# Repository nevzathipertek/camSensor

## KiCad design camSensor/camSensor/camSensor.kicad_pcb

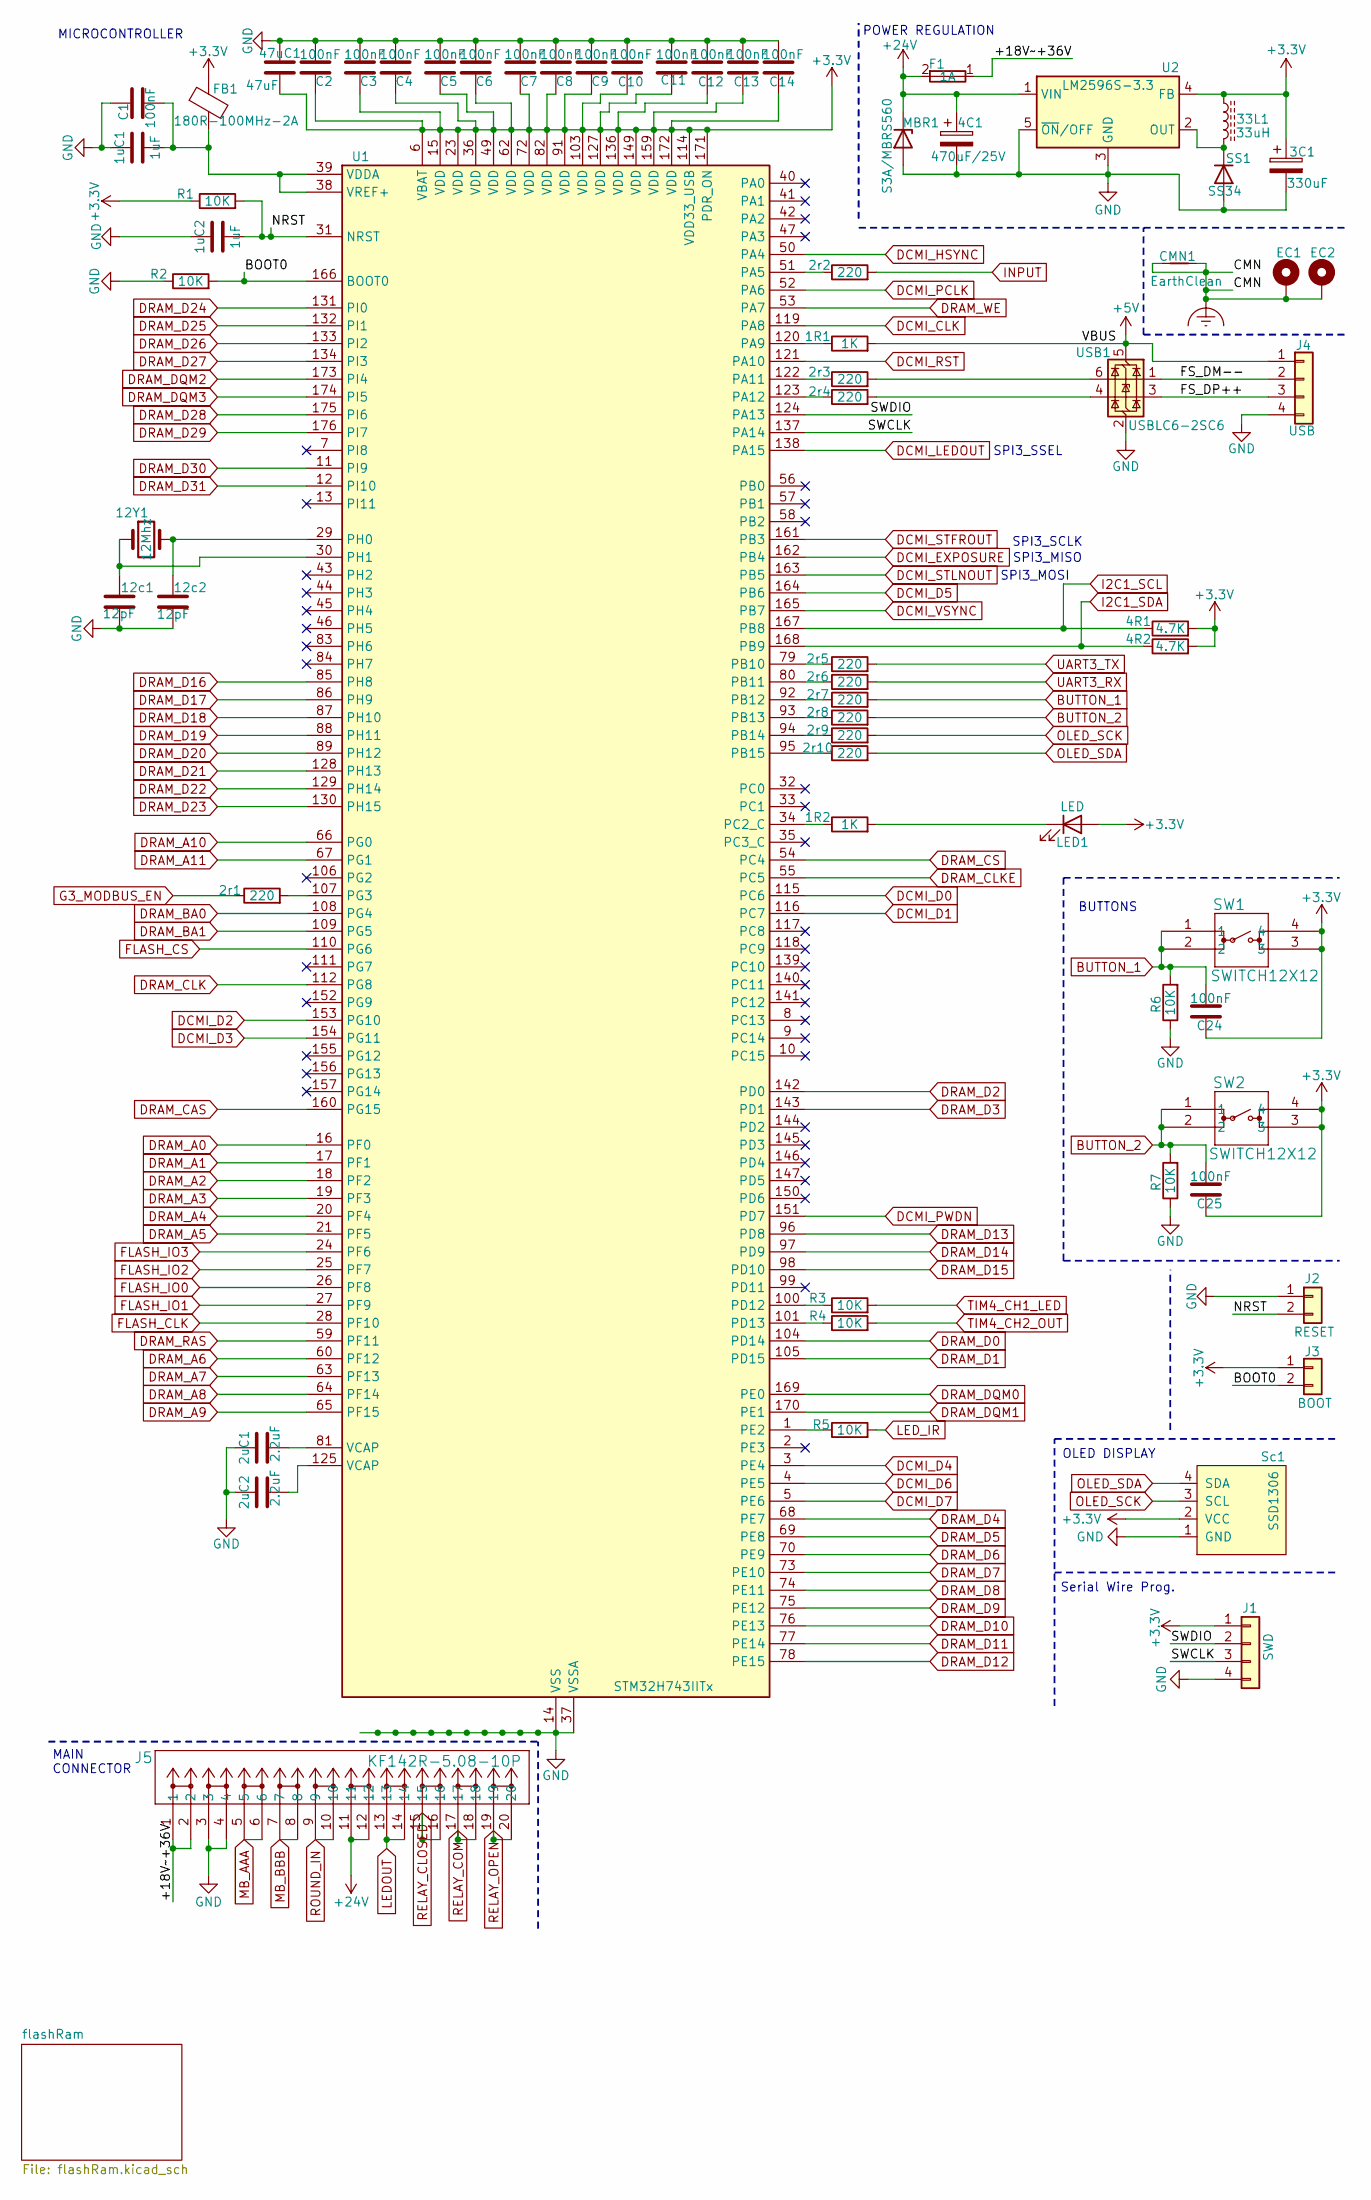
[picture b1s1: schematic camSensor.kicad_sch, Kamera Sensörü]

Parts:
1R1, 1R2: 1K; R_0603_1608Metric
1uC1, 1uC2: 1uF; C_0603_1608Metric
2r1, 2r2, 2r3, 2r4, 2r5, 2r6, 2r7, 2r8, 2r9, 2r10: 220; R_0603_1608Metric
2uC1, 2uC2: 2.2uF; C_0603_1608Metric
3C1: 330uF; CP_Elec_6.3x5.9
4C1: 470uF/25V; CP_Elec_10x10
4R1, 4R2: 4.7K; R_0603_1608Metric
12Y1: 12Mhz; Crystal_SMD_HC49-SD
12c1, 12c2: 12pF; C_0603_1608Metric
33L1: 33uH; L_Bourns_SRP7028A_7.3x6.6mm
47uC1: 47uF; C_0805_2012Metric
C1, C2, C3, C4, C5, C6, C7, C8, C9, C10, C11, C12, C13, C14, C24, C25: 100nF; C_0603_1608Metric
CMN1: EarthClean; NetTie-2_SMD_Pad0.5mm
EC1, EC2: MountingHole_Pad; MountingHole_2.2mm_M2_Pad
F1: 1A; CONN02_FUSEBLOCK_22P6X9_LTF
FB1: 180R-100MHz-2A; L_0805_2012Metric
J1: SWD; PinSocket_1x04_P2.54mm_Vertical
J2: RESET; PinHeader_1x02_P2.54mm_Vertical
J3: BOOT; PinHeader_1x02_P2.54mm_Vertical
J4: USB; PinHeader_1x04_P2.54mm_Vertical
J5: KF142R-5.08-10P; CONN_KF142R-5.08-10P_CKE
LED1: LED; LED_0603_1608Metric
MBR1: S3A/MBRS560; D_SMC
R1, R2, R3, R4, R5, R6, R7: 10K; R_0603_1608Metric
SS1: SS34; D_SMB
SW1, SW2: SWITCH12X12; 1571217-3_TEC
Sc1: SSD1306; 128x64OLED
U1: STM32H743IITx; LQFP-176_24x24mm_P0.5mm
U2: LM2596S-3.3; TO-263-5_TabPin3
USB1: USBLC6-2SC6; SOT-23-6

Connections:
+3.3V: 3C1.1, 4R1.2, 4R2.2, 33L1.1, 47uC1.2, C2.1, C3.1, C4.1, C5.1, C6.1, C7.1, C8.1, C9.1, C10.1, C11.1, C12.1, C13.1, C14.1, C24.1, C25.1, FB1.1, J1.1, J3.1, LED1.2 (A), R1.1, SW1.3, SW1.4, SW2.3, SW2.4, Sc1.2 (VCC), U1.6 (VBAT), U1.15 (VDD), U1.23 (VDD), U1.36 (VDD), U1.49 (VDD), U1.62 (VDD), U1.72 (VDD), U1.82 (VDD), U1.91 (VDD), U1.103 (VDD), U1.114 (VDD33_USB), U1.127 (VDD), U1.136 (VDD), U1.149 (VDD), U1.159 (VDD), U1.171 (PDR_ON), U1.172 (VDD), U2.4 (FB); also elsewhere on the board
+5V: 1R1.2, J4.1, USB1.5 (VBUS)
+24V: 4C1.1, F1.2, J5.11, J5.12, MBR1.1 (K), U2.1 (VIN); also elsewhere on the board
/+18V~+36V: F1.1, J5.1, J5.2
/BOOT0: J3.2, R2.2, U1.166 (BOOT0)
/FS_DM--: J4.2, USB1.1 (I/O1)
/FS_DP++: J4.3, USB1.3 (I/O2)
/NRST: 1uC2.2, J2.2, R1.2, U1.31 (NRST)
/SWCLK: J1.3, U1.137 (PA14)
/SWDIO: J1.2, U1.124 (PA13)
BUTTON_1: 2r7.2, C24.2, R6.2, SW1.1, SW1.2
BUTTON_2: 2r8.2, C25.2, R7.2, SW2.1, SW2.2
DCMI_CLK: U1.119 (PA8); also elsewhere on the board
DCMI_D0: U1.115 (PC6); also elsewhere on the board
DCMI_D1: U1.116 (PC7); also elsewhere on the board
DCMI_D2: U1.153 (PG10); also elsewhere on the board
DCMI_D3: U1.154 (PG11); also elsewhere on the board
DCMI_D4: U1.3 (PE4); also elsewhere on the board
DCMI_D5: U1.164 (PB6); also elsewhere on the board
DCMI_D6: U1.4 (PE5); also elsewhere on the board
DCMI_D7: U1.5 (PE6); also elsewhere on the board
DCMI_EXPOSURE: U1.162 (PB4); also elsewhere on the board
DCMI_HSYNC: U1.50 (PA4); also elsewhere on the board
DCMI_LEDOUT: U1.138 (PA15); also elsewhere on the board
DCMI_PCLK: U1.52 (PA6); also elsewhere on the board
DCMI_PWDN: U1.151 (PD7); also elsewhere on the board
DCMI_RST: U1.121 (PA10); also elsewhere on the board
DCMI_STFROUT: U1.161 (PB3); also elsewhere on the board
DCMI_STLNOUT: U1.163 (PB5); also elsewhere on the board
DCMI_VSYNC: U1.165 (PB7); also elsewhere on the board
DRAM_A0: U1.16 (PF0); also elsewhere on the board
DRAM_A1: U1.17 (PF1); also elsewhere on the board
DRAM_A2: U1.18 (PF2); also elsewhere on the board
DRAM_A3: U1.19 (PF3); also elsewhere on the board
DRAM_A4: U1.20 (PF4); also elsewhere on the board
DRAM_A5: U1.21 (PF5); also elsewhere on the board
DRAM_A6: U1.60 (PF12); also elsewhere on the board
DRAM_A7: U1.63 (PF13); also elsewhere on the board
DRAM_A8: U1.64 (PF14); also elsewhere on the board
DRAM_A9: U1.65 (PF15); also elsewhere on the board
DRAM_A10: U1.66 (PG0); also elsewhere on the board
DRAM_A11: U1.67 (PG1); also elsewhere on the board
DRAM_BA0: U1.108 (PG4); also elsewhere on the board
DRAM_BA1: U1.109 (PG5); also elsewhere on the board
DRAM_CAS: U1.160 (PG15); also elsewhere on the board
DRAM_CLK: U1.112 (PG8); also elsewhere on the board
DRAM_CLKE: U1.55 (PC5); also elsewhere on the board
DRAM_CS: U1.54 (PC4); also elsewhere on the board
DRAM_D0: U1.104 (PD14); also elsewhere on the board
DRAM_D1: U1.105 (PD15); also elsewhere on the board
DRAM_D2: U1.142 (PD0); also elsewhere on the board
DRAM_D3: U1.143 (PD1); also elsewhere on the board
DRAM_D4: U1.68 (PE7); also elsewhere on the board
DRAM_D5: U1.69 (PE8); also elsewhere on the board
DRAM_D6: U1.70 (PE9); also elsewhere on the board
DRAM_D7: U1.73 (PE10); also elsewhere on the board
DRAM_D8: U1.74 (PE11); also elsewhere on the board
DRAM_D9: U1.75 (PE12); also elsewhere on the board
DRAM_D10: U1.76 (PE13); also elsewhere on the board
DRAM_D11: U1.77 (PE14); also elsewhere on the board
DRAM_D12: U1.78 (PE15); also elsewhere on the board
DRAM_D13: U1.96 (PD8); also elsewhere on the board
DRAM_D14: U1.97 (PD9); also elsewhere on the board
DRAM_D15: U1.98 (PD10); also elsewhere on the board
DRAM_D16: U1.85 (PH8); also elsewhere on the board
DRAM_D17: U1.86 (PH9); also elsewhere on the board
DRAM_D18: U1.87 (PH10); also elsewhere on the board
DRAM_D19: U1.88 (PH11); also elsewhere on the board
DRAM_D20: U1.89 (PH12); also elsewhere on the board
DRAM_D21: U1.128 (PH13); also elsewhere on the board
DRAM_D22: U1.129 (PH14); also elsewhere on the board
DRAM_D23: U1.130 (PH15); also elsewhere on the board
DRAM_D24: U1.131 (PI0); also elsewhere on the board
DRAM_D25: U1.132 (PI1); also elsewhere on the board
DRAM_D26: U1.133 (PI2); also elsewhere on the board
DRAM_D27: U1.134 (PI3); also elsewhere on the board
DRAM_D28: U1.175 (PI6); also elsewhere on the board
DRAM_D29: U1.176 (PI7); also elsewhere on the board
DRAM_D30: U1.11 (PI9); also elsewhere on the board
DRAM_D31: U1.12 (PI10); also elsewhere on the board
DRAM_DQM0: U1.169 (PE0); also elsewhere on the board
DRAM_DQM1: U1.170 (PE1); also elsewhere on the board
DRAM_DQM2: U1.173 (PI4); also elsewhere on the board
DRAM_DQM3: U1.174 (PI5); also elsewhere on the board
DRAM_RAS: U1.59 (PF11); also elsewhere on the board
DRAM_WE: U1.53 (PA7); also elsewhere on the board
Earth_Clean: CMN1.1, CMN1.2, EC1.1, EC2.1
FLASH_CLK: U1.28 (PF10); also elsewhere on the board
FLASH_CS: U1.110 (PG6); also elsewhere on the board
FLASH_IO0: U1.26 (PF8); also elsewhere on the board
FLASH_IO1: U1.27 (PF9); also elsewhere on the board
FLASH_IO2: U1.25 (PF7); also elsewhere on the board
FLASH_IO3: U1.24 (PF6); also elsewhere on the board
G3_MODBUS_EN: 2r1.1; also elsewhere on the board
GND: 1uC1.1, 1uC2.1, 2uC1.1, 2uC2.1, 3C1.2, 4C1.2, 12c1.2, 12c2.2, 47uC1.1, C1.1, C2.2, C3.2, C4.2, C5.2, C6.2, C7.2, C8.2, C9.2, C10.2, C11.2, C12.2, C13.2, C14.2, J1.4, J2.1, J4.4, J5.3, J5.4, MBR1.2 (A), R2.1, R6.1, R7.1, SS1.2 (A), Sc1.1 (GND), U1.14 (VSS), U1.22 (VSS), U1.37 (VSSA), U1.48 (VSS), U1.61 (VSS), U1.71 (VSS), U1.90 (VSS), U1.102 (VSS), U1.113 (VSS), U1.126 (VSS), U1.135 (VSS), U1.148 (VSS), U1.158 (VSS), U2.3 (GND), U2.5 (~ON/OFF), USB1.2 (GND); also elsewhere on the board
I2C1_SCL: 4R1.1, U1.167 (PB8); also elsewhere on the board
I2C1_SDA: 4R2.1, U1.168 (PB9); also elsewhere on the board
INPUT: 2r2.2; also elsewhere on the board
LEDOUT: J5.13, J5.14; also elsewhere on the board
LED_IR: R5.2; also elsewhere on the board
MB_AAA: J5.5, J5.6; also elsewhere on the board
MB_BBB: J5.7, J5.8; also elsewhere on the board
unnamed: 2r3.2, USB1.6 (I/O1)
unnamed: 2r4.2, USB1.4 (I/O2)
unnamed: 2uC1.2, U1.81 (VCAP)
unnamed: 2uC2.2, U1.125 (VCAP)
unnamed: 1R2.2, LED1.1 (K)
unnamed: 33L1.2, SS1.1 (K), U2.2 (OUT)
unnamed: 2r2.1, U1.51 (PA5)
unnamed: 1R1.1, U1.120 (PA9)
unnamed: 2r3.1, U1.122 (PA11)
unnamed: 2r4.1, U1.123 (PA12)
unnamed: 2r5.1, U1.79 (PB10)
unnamed: 2r6.1, U1.80 (PB11)
unnamed: 2r7.1, U1.92 (PB12)
unnamed: 2r8.1, U1.93 (PB13)
unnamed: 2r9.1, U1.94 (PB14)
unnamed: 2r10.1, U1.95 (PB15)
unnamed: 1R2.1, U1.34 (PC2_C)
unnamed: R3.1, U1.100 (PD12)
unnamed: R4.1, U1.101 (PD13)
unnamed: R5.1, U1.1 (PE2)
unnamed: 2r1.2, U1.107 (PG3)
unnamed: 12Y1.2, 12c2.1, U1.29 (PH0)
unnamed: 12Y1.1, 12c1.1, U1.30 (PH1)
unnamed: 1uC1.2, C1.2, FB1.2, U1.38 (VREF+), U1.39 (VDDA)
OLED_SCK: 2r9.2, Sc1.3 (SCL)
OLED_SDA: 2r10.2, Sc1.4 (SDA)
RELAY_CLOSED: J5.15, J5.16; also elsewhere on the board
RELAY_COM: J5.17, J5.18; also elsewhere on the board
RELAY_OPEN: J5.19, J5.20; also elsewhere on the board
ROUND_IN: J5.9, J5.10; also elsewhere on the board
TIM4_CH1_LED: R3.2; also elsewhere on the board
TIM4_CH2_OUT: R4.2; also elsewhere on the board
UART3_RX: 2r6.2; also elsewhere on the board
UART3_TX: 2r5.2; also elsewhere on the board

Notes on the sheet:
OLED DISPLAY
Serial Wire Prog.
SPI3_SCLK
SPI3_MISO
POWER REGULATION
MAIN CONNECTOR
SPI3_MOSI
BUTTONS
MICROCONTROLLER
SPI3_SSEL

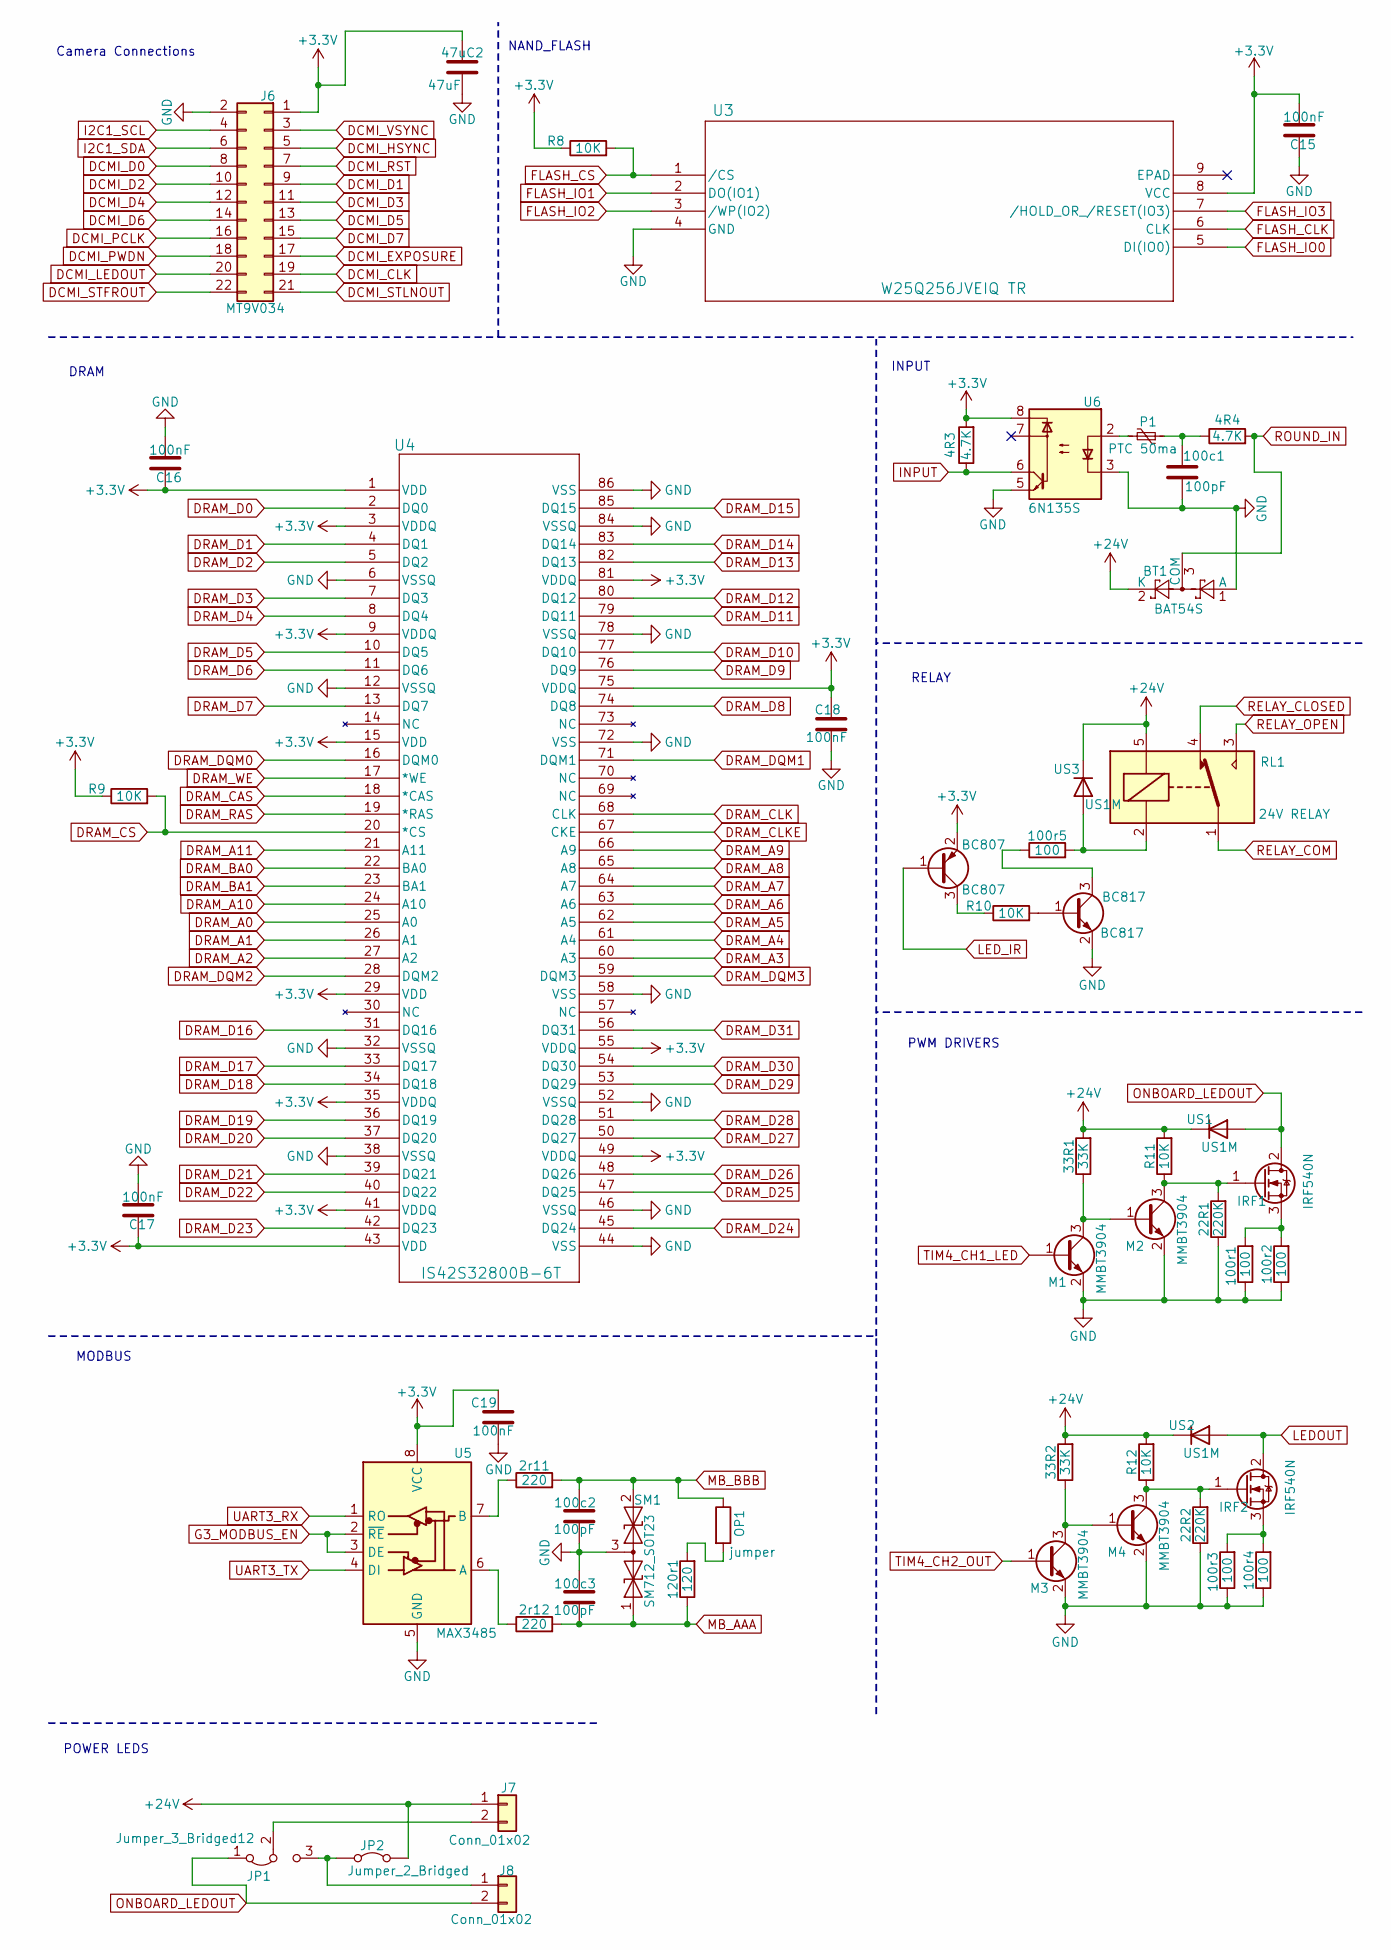
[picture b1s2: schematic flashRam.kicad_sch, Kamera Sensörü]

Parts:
2r11, 2r12: 220; R_0603_1608Metric
4R3, 4R4: 4.7K; R_0603_1608Metric
22R1, 22R2: 220K; R_0603_1608Metric
33R1, 33R2: 33K; R_0603_1608Metric
47uC2: 47uF; C_0805_2012Metric
100c1, 100c2, 100c3: 100pF; C_0603_1608Metric
100r1, 100r2, 100r3, 100r4, 100r5: 100; R_2512_6332Metric_Pad1.40x3.35mm_HandSolder
120r1: 120; R_0603_1608Metric
BC807: BC807; SOT-23
BC817: BC817; SOT-23
BT1: BAT54S; SOT-23
C15, C16, C17, C18, C19: 100nF; C_0603_1608Metric
IRF1, IRF2: IRF540N; TO-263-2
J6: MT9V034; PinHeader_2x11_P2.54mm_Vertical
J7, J8: Conn_01x02; PinHeader_1x02_P2.54mm_Vertical
JP1: Jumper_3_Bridged12; SolderJumper-3_P1.3mm_Bridged12_RoundedPad1.0x1.5mm
JP2: Jumper_2_Bridged; SolderJumper-2_P1.3mm_Bridged_RoundedPad1.0x1.5mm
M1, M2, M3, M4: MMBT3904; SOT-23
OP1: jumper; SolderJumper-2_P1.3mm_Bridged_RoundedPad1.0x1.5mm
P1: PTC 50ma; Fuse_0805_2012Metric
R8, R9, R10, R11, R12: 10K; R_0603_1608Metric
RL1: 24V RELAY; Relay_SPDT_SANYOU_SRD_Series_Form_C
SM1: SM712_SOT23; SOT-23
U3: W25Q256JVEIQ TR; WSON8_E_WIN
U4: IS42S32800B-6T; TSOP-86_11P9X22P4_ISI
U5: MAX3485; SOIC-8_3.9x4.9mm_P1.27mm
U6: 6N135S; SMDIP-8_W9.53mm
US1, US2, US3: US1M; D_SMA

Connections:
+3.3V: 4R3.2, 47uC2.1, BC807.2 (E), C15.2, C16.1, C17.1, C18.1, C19.1, J6.1, R8.1, R9.1, U3.8 (VCC), U4.1 (VDD), U4.3 (VDDQ), U4.9 (VDDQ), U4.15 (VDD), U4.29 (VDD), U4.35 (VDDQ), U4.41 (VDDQ), U4.43 (VDD), U4.49 (VDDQ), U4.55 (VDDQ), U4.75 (VDDQ), U4.81 (VDDQ), U5.8 (VCC), U6.8; also elsewhere on the board
+24V: 33R1.2, 33R2.2, BT1.2 (K), J7.1, JP2.2 (B), R11.2, R12.2, RL1.5, US1.1 (K), US2.1 (K), US3.1 (K); also elsewhere on the board
DCMI_CLK: J6.19; also elsewhere on the board
DCMI_D0: J6.8; also elsewhere on the board
DCMI_D1: J6.9; also elsewhere on the board
DCMI_D2: J6.10; also elsewhere on the board
DCMI_D3: J6.11; also elsewhere on the board
DCMI_D4: J6.12; also elsewhere on the board
DCMI_D5: J6.13; also elsewhere on the board
DCMI_D6: J6.14; also elsewhere on the board
DCMI_D7: J6.15; also elsewhere on the board
DCMI_EXPOSURE: J6.17; also elsewhere on the board
DCMI_HSYNC: J6.5; also elsewhere on the board
DCMI_LEDOUT: J6.20; also elsewhere on the board
DCMI_PCLK: J6.16; also elsewhere on the board
DCMI_PWDN: J6.18; also elsewhere on the board
DCMI_RST: J6.7; also elsewhere on the board
DCMI_STFROUT: J6.22; also elsewhere on the board
DCMI_STLNOUT: J6.21; also elsewhere on the board
DCMI_VSYNC: J6.3; also elsewhere on the board
DRAM_A0: U4.25 (A0); also elsewhere on the board
DRAM_A1: U4.26 (A1); also elsewhere on the board
DRAM_A2: U4.27 (A2); also elsewhere on the board
DRAM_A3: U4.60 (A3); also elsewhere on the board
DRAM_A4: U4.61 (A4); also elsewhere on the board
DRAM_A5: U4.62 (A5); also elsewhere on the board
DRAM_A6: U4.63 (A6); also elsewhere on the board
DRAM_A7: U4.64 (A7); also elsewhere on the board
DRAM_A8: U4.65 (A8); also elsewhere on the board
DRAM_A9: U4.66 (A9); also elsewhere on the board
DRAM_A10: U4.24 (A10); also elsewhere on the board
DRAM_A11: U4.21 (A11); also elsewhere on the board
DRAM_BA0: U4.22 (BA0); also elsewhere on the board
DRAM_BA1: U4.23 (BA1); also elsewhere on the board
DRAM_CAS: U4.18 (*CAS); also elsewhere on the board
DRAM_CLK: U4.68 (CLK); also elsewhere on the board
DRAM_CLKE: U4.67 (CKE); also elsewhere on the board
DRAM_CS: R9.2, U4.20 (*CS); also elsewhere on the board
DRAM_D0: U4.2 (DQ0); also elsewhere on the board
DRAM_D1: U4.4 (DQ1); also elsewhere on the board
DRAM_D2: U4.5 (DQ2); also elsewhere on the board
DRAM_D3: U4.7 (DQ3); also elsewhere on the board
DRAM_D4: U4.8 (DQ4); also elsewhere on the board
DRAM_D5: U4.10 (DQ5); also elsewhere on the board
DRAM_D6: U4.11 (DQ6); also elsewhere on the board
DRAM_D7: U4.13 (DQ7); also elsewhere on the board
DRAM_D8: U4.74 (DQ8); also elsewhere on the board
DRAM_D9: U4.76 (DQ9); also elsewhere on the board
DRAM_D10: U4.77 (DQ10); also elsewhere on the board
DRAM_D11: U4.79 (DQ11); also elsewhere on the board
DRAM_D12: U4.80 (DQ12); also elsewhere on the board
DRAM_D13: U4.82 (DQ13); also elsewhere on the board
DRAM_D14: U4.83 (DQ14); also elsewhere on the board
DRAM_D15: U4.85 (DQ15); also elsewhere on the board
DRAM_D16: U4.31 (DQ16); also elsewhere on the board
DRAM_D17: U4.33 (DQ17); also elsewhere on the board
DRAM_D18: U4.34 (DQ18); also elsewhere on the board
DRAM_D19: U4.36 (DQ19); also elsewhere on the board
DRAM_D20: U4.37 (DQ20); also elsewhere on the board
DRAM_D21: U4.39 (DQ21); also elsewhere on the board
DRAM_D22: U4.40 (DQ22); also elsewhere on the board
DRAM_D23: U4.42 (DQ23); also elsewhere on the board
DRAM_D24: U4.45 (DQ24); also elsewhere on the board
DRAM_D25: U4.47 (DQ25); also elsewhere on the board
DRAM_D26: U4.48 (DQ26); also elsewhere on the board
DRAM_D27: U4.50 (DQ27); also elsewhere on the board
DRAM_D28: U4.51 (DQ28); also elsewhere on the board
DRAM_D29: U4.53 (DQ29); also elsewhere on the board
DRAM_D30: U4.54 (DQ30); also elsewhere on the board
DRAM_D31: U4.56 (DQ31); also elsewhere on the board
DRAM_DQM0: U4.16 (DQM0); also elsewhere on the board
DRAM_DQM1: U4.71 (DQM1); also elsewhere on the board
DRAM_DQM2: U4.28 (DQM2); also elsewhere on the board
DRAM_DQM3: U4.59 (DQM3); also elsewhere on the board
DRAM_RAS: U4.19 (*RAS); also elsewhere on the board
DRAM_WE: U4.17 (*WE); also elsewhere on the board
FLASH_CLK: U3.6 (CLK); also elsewhere on the board
FLASH_CS: R8.2, U3.1 (/CS); also elsewhere on the board
FLASH_IO0: U3.5 (DI(IO0)); also elsewhere on the board
FLASH_IO1: U3.2 (DO(IO1)); also elsewhere on the board
FLASH_IO2: U3.3 (/WP(IO2)); also elsewhere on the board
FLASH_IO3: U3.7 (/HOLD_OR_/RESET(IO3)); also elsewhere on the board
G3_MODBUS_EN: U5.2 (~RE), U5.3 (DE); also elsewhere on the board
GND: 22R1.1, 22R2.1, 47uC2.2, 100c1.2, 100c2.2, 100c3.1, 100r1.1, 100r2.1, 100r3.1, 100r4.1, BC817.2 (E), BT1.1 (A), C15.1, C16.2, C17.2, C18.2, C19.2, J6.2, M1.2 (E), M2.2 (E), M3.2 (E), M4.2 (E), SM1.3 (common), U3.4 (GND), U4.6 (VSSQ), U4.12 (VSSQ), U4.32 (VSSQ), U4.38 (VSSQ), U4.44 (VSS), U4.46 (VSSQ), U4.52 (VSSQ), U4.58 (VSS), U4.72 (VSS), U4.78 (VSSQ), U4.84 (VSSQ), U4.86 (VSS), U5.5 (GND), U6.3, U6.5; also elsewhere on the board
I2C1_SCL: J6.4; also elsewhere on the board
I2C1_SDA: J6.6; also elsewhere on the board
INPUT: 4R3.1, U6.6; also elsewhere on the board
LEDOUT: IRF2.2 (D), US2.2 (A); also elsewhere on the board
LED_IR: BC807.1 (B); also elsewhere on the board
MB_AAA: 2r12.2, 100c3.2, 120r1.1, SM1.1 (A1); also elsewhere on the board
MB_BBB: 2r11.2, 100c2.1, OP1.1, SM1.2 (A2); also elsewhere on the board
unnamed: 4R4.1, 100c1.1, P1.1
unnamed: 120r1.2, OP1.2
unnamed: BC807.3 (C), R10.1
unnamed: BC817.1 (B), R10.2
unnamed: 100r5.1, BC817.3 (C)
unnamed: 22R1.2, IRF1.1 (G), M2.3 (C), R11.1
unnamed: 100r1.2, 100r2.2, IRF1.3 (S)
unnamed: 22R2.2, IRF2.1 (G), M4.3 (C), R12.1
unnamed: 100r3.2, 100r4.2, IRF2.3 (S)
unnamed: J7.2, JP1.2 (C)
unnamed: J8.1, JP1.3 (B), JP2.1 (A)
unnamed: 33R1.1, M1.3 (C), M2.1 (B)
unnamed 119: 33R2.1, M3.3 (C), M4.1 (B); also elsewhere on the board
unnamed: P1.2, U6.2
unnamed: 2r12.1, U5.6 (A)
unnamed: 2r11.1, U5.7 (B)
unnamed: 100r5.2, RL1.2, US3.2 (A)
ONBOARD_LEDOUT: IRF1.2 (D), J8.2, JP1.1 (A), US1.2 (A)
RELAY_CLOSED: RL1.4; also elsewhere on the board
RELAY_COM: RL1.1; also elsewhere on the board
RELAY_OPEN: RL1.3; also elsewhere on the board
ROUND_IN: 4R4.2, BT1.3 (COM); also elsewhere on the board
TIM4_CH1_LED: M1.1 (B); also elsewhere on the board
TIM4_CH2_OUT: M3.1 (B); also elsewhere on the board
UART3_RX: U5.1 (RO); also elsewhere on the board
UART3_TX: U5.4 (DI); also elsewhere on the board

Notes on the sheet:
Camera Connections
NAND_FLASH
RELAY
PWM DRIVERS
MODBUS
INPUT
POWER LEDS
DRAM

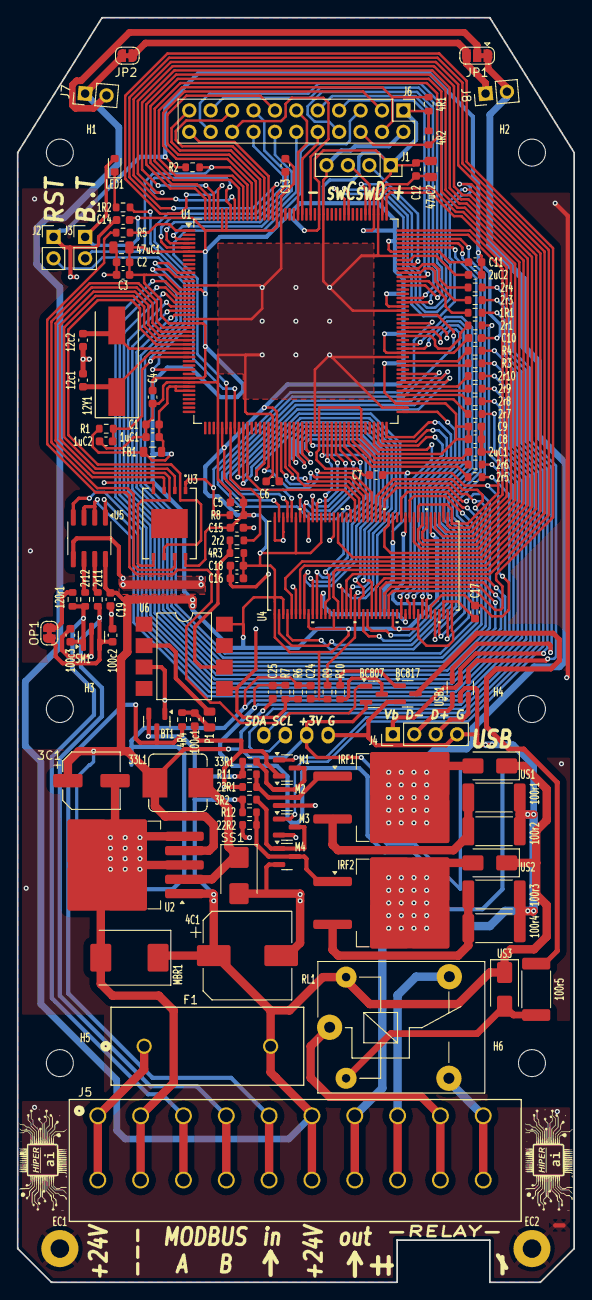
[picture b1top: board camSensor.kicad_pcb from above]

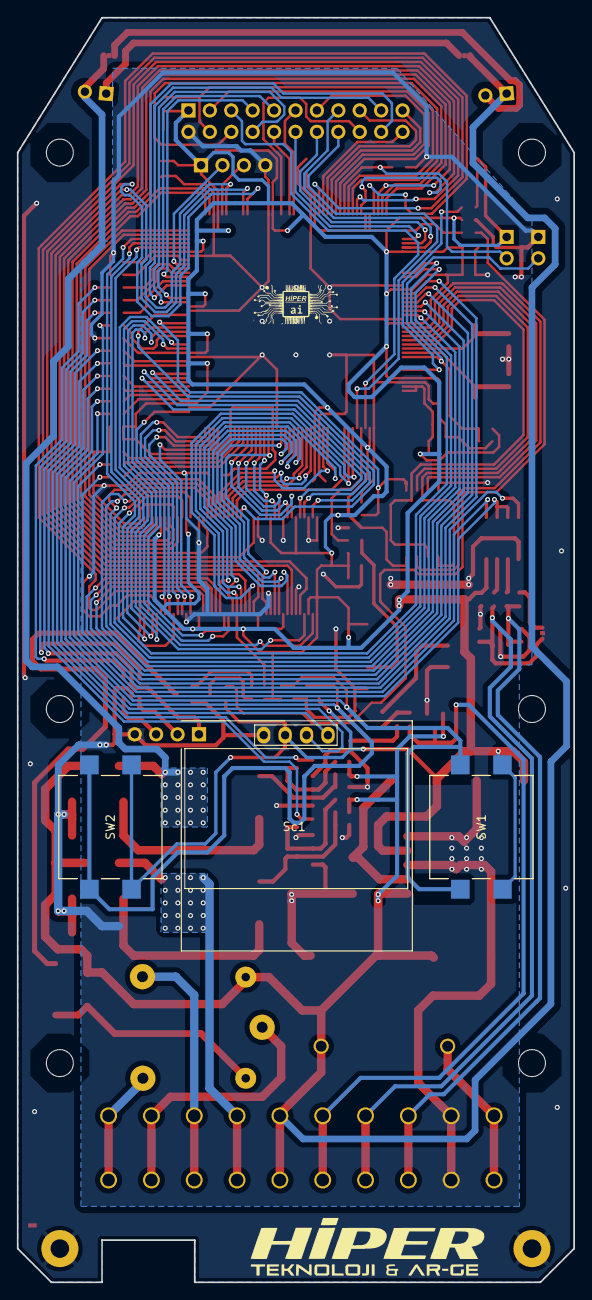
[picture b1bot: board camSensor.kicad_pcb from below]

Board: 2 copper layers, 66.0 x 150.0 mm, 130 parts (5 on the bottom side), 154 nets.

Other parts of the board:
3R2: 33K; R_0603_1608Metric
H1, H2, H3, H4, H5, H6: MountingHole_3.2mm_M3
ai: LOGO
ai#2, ai#3: LOGO
hiper: LOGO

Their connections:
+24V: 3R2.2; also elsewhere on the board
unnamed 119: 3R2.1; also elsewhere on the board

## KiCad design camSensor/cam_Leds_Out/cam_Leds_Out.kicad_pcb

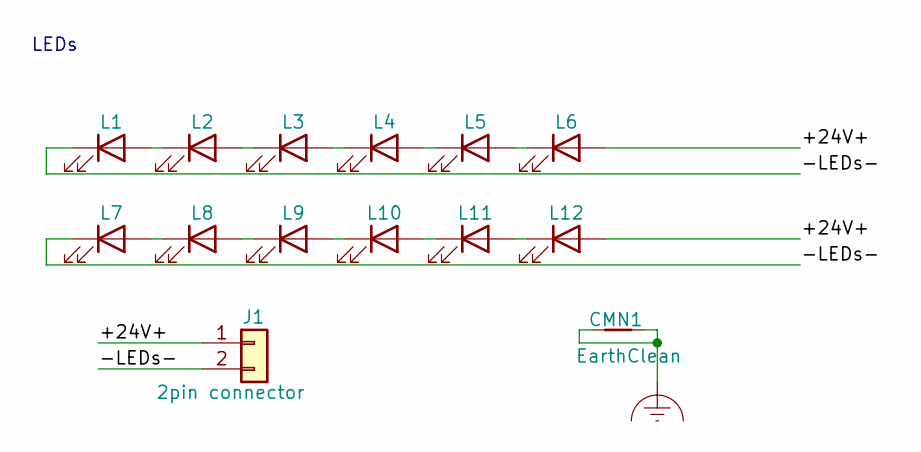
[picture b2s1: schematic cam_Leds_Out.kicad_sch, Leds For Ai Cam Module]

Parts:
CMN1: EarthClean; NetTie-2_SMD_Pad0.5mm
J1: 2pin connector; PinHeader_1x02_P2.54mm_Vertical
L1, L2, L3, L4, L5, L6, L7, L8, L9, L10, L11, L12: LED; LED_PLCC_2835

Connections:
/+24V+: J1.1, L6.2 (A), L12.2 (A)
/-LEDs-: J1.2, L1.1 (K), L7.1 (K)
Earth_Clean: CMN1.1, CMN1.2
unnamed: L1.2 (A), L2.1 (K)
unnamed: L2.2 (A), L3.1 (K)
unnamed: L3.2 (A), L4.1 (K)
unnamed: L4.2 (A), L5.1 (K)
unnamed: L5.2 (A), L6.1 (K)
unnamed: L7.2 (A), L8.1 (K)
unnamed: L8.2 (A), L9.1 (K)
unnamed: L10.2 (A), L11.1 (K)
unnamed: L9.2 (A), L10.1 (K)
unnamed: L11.2 (A), L12.1 (K)

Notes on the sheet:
LEDs

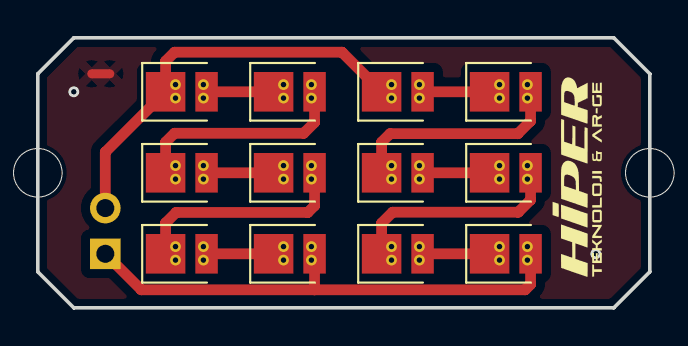
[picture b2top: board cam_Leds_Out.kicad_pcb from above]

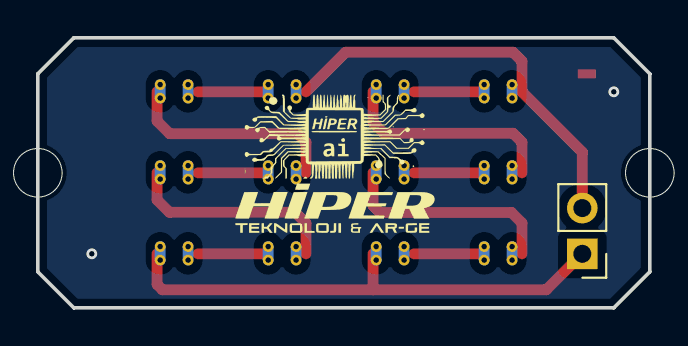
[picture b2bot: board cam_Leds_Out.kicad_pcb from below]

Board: 2 copper layers, 34.0 x 15.0 mm, 19 parts (3 on the bottom side), 13 nets.

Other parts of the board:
H1, H1#2: MountingHole_2.7mm_M2.5
ai: LOGO
hiper: LOGO
hiper#2: LOGO

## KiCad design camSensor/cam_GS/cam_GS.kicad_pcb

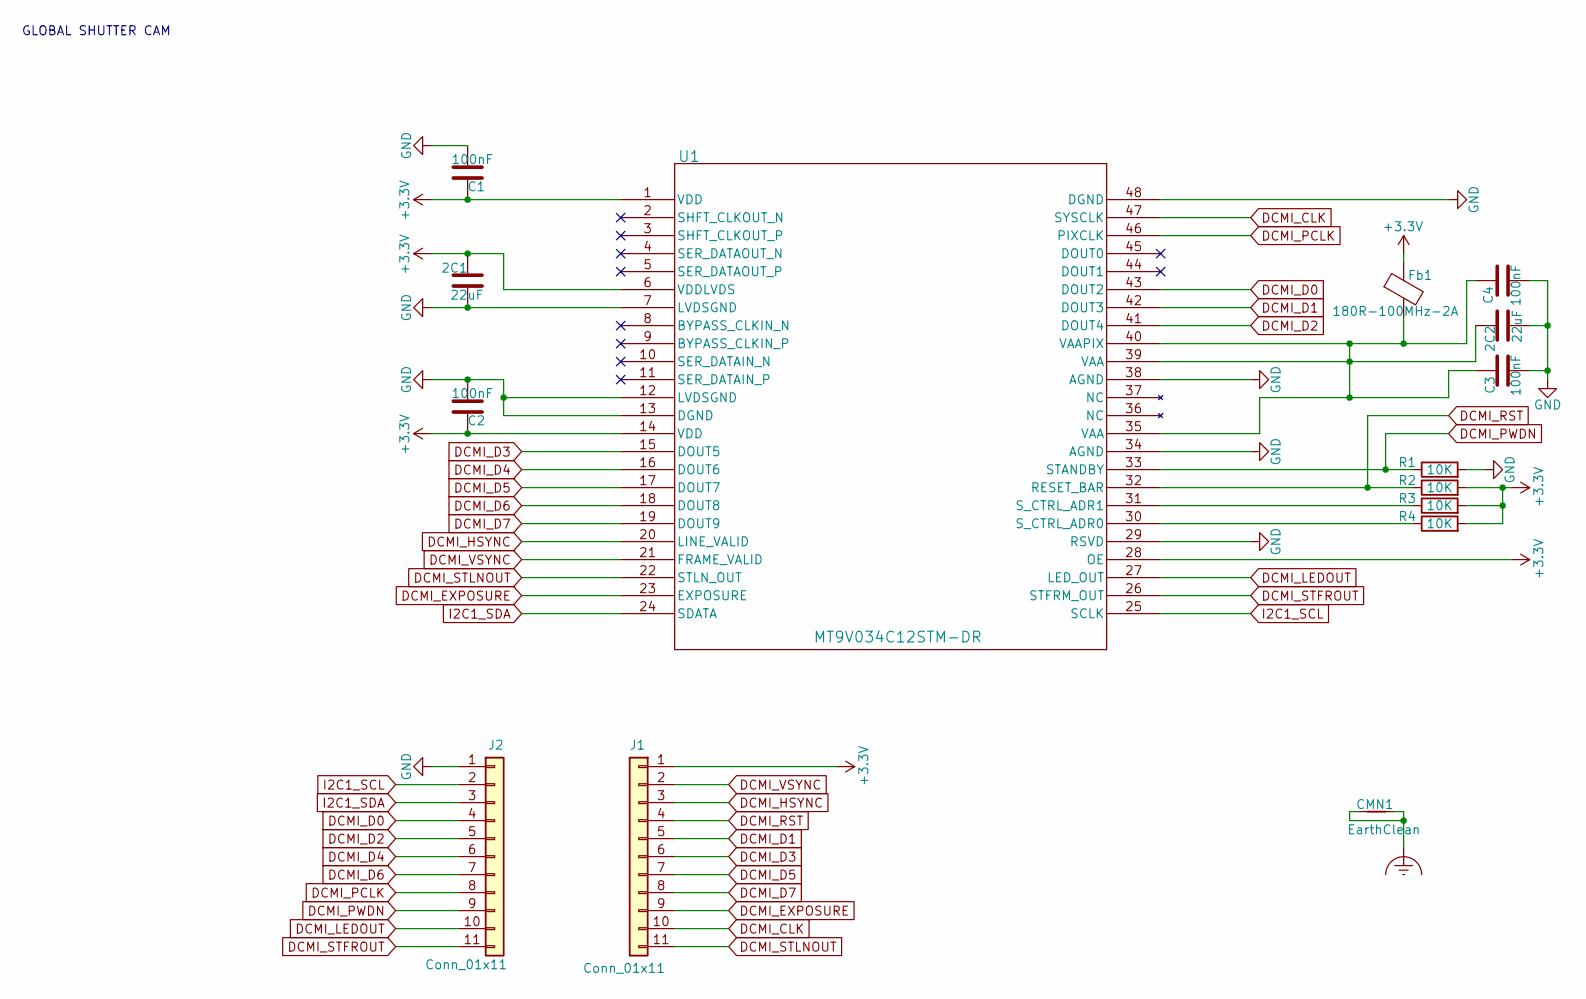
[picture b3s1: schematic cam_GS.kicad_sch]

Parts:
2C1, 2C2: 22uF; C_0603_1608Metric
C1, C2, C3, C4: 100nF; C_0603_1608Metric
CMN1: EarthClean; NetTie-2_SMD_Pad0.5mm
Fb1: 180R-100MHz-2A; L_0805_2012Metric
J1, J2: Conn_01x11; PinHeader_1x11_P2.54mm_Vertical
R1, R2, R3, R4: 10K; R_0603_1608Metric
U1: MT9V034C12STM-DR; CLCC48_11p43x11p43_848AN_OSI

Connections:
+3.3V: 2C1.1, C1.1, C2.1, Fb1.1, J1.1, R2.2, R3.2, R4.2, U1.1 (VDD), U1.6 (VDDLVDS), U1.14 (VDD), U1.28 (OE)
DCMI_CLK: J1.10, U1.47 (SYSCLK)
DCMI_D0: J2.4, U1.43 (DOUT2)
DCMI_D1: J1.5, U1.42 (DOUT3)
DCMI_D2: J2.5, U1.41 (DOUT4)
DCMI_D3: J1.6, U1.15 (DOUT5)
DCMI_D4: J2.6, U1.16 (DOUT6)
DCMI_D5: J1.7, U1.17 (DOUT7)
DCMI_D6: J2.7, U1.18 (DOUT8)
DCMI_D7: J1.8, U1.19 (DOUT9)
DCMI_EXPOSURE: J1.9, U1.23 (EXPOSURE)
DCMI_HSYNC: J1.3, U1.20 (LINE_VALID)
DCMI_LEDOUT: J2.10, U1.27 (LED_OUT)
DCMI_PCLK: J2.8, U1.46 (PIXCLK)
DCMI_PWDN: J2.9, R1.1, U1.33 (STANDBY)
DCMI_RST: J1.4, R2.1, U1.32 (RESET_BAR)
DCMI_STFROUT: J2.11, U1.26 (STFRM_OUT)
DCMI_STLNOUT: J1.11, U1.22 (STLN_OUT)
DCMI_VSYNC: J1.2, U1.21 (FRAME_VALID)
Earth_Clean: CMN1.1, CMN1.2
GND: 2C1.2, 2C2.2, C1.2, C2.2, C3.2, C4.2, J2.1, R1.2, U1.7 (LVDSGND), U1.12 (LVDSGND), U1.13 (DGND), U1.29 (RSVD), U1.34 (AGND), U1.38 (AGND), U1.48 (DGND)
I2C1_SCL: J2.2, U1.25 (SCLK)
I2C1_SDA: J2.3, U1.24 (SDATA)
unnamed: R4.1, U1.30 (S_CTRL_ADR0)
unnamed: R3.1, U1.31 (S_CTRL_ADR1)
unnamed: 2C2.1, C3.1, C4.1, Fb1.2, U1.35 (VAA), U1.39 (VAA), U1.40 (VAAPIX)

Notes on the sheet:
GLOBAL SHUTTER CAM

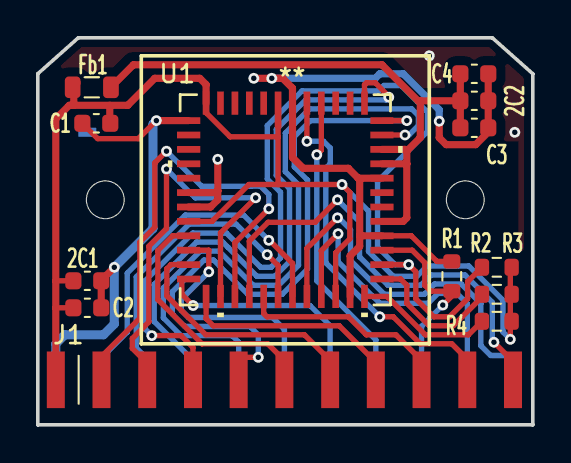
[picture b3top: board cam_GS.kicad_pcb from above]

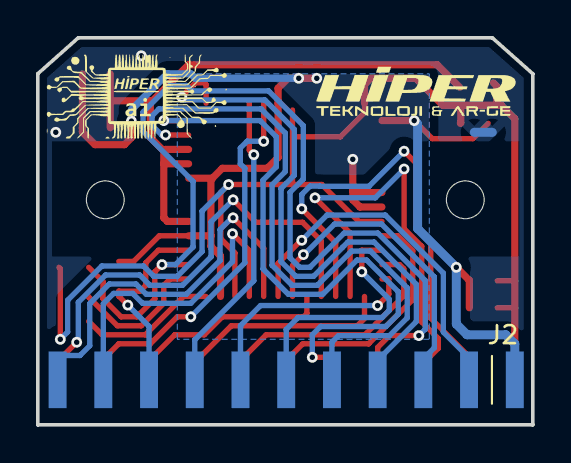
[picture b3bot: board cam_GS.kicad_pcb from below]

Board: 2 copper layers, 27.5 x 21.5 mm, 19 parts (4 on the bottom side), 26 nets.

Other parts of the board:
H1, H2: MountingHole_2.1mm
ai: LOGO
hiper: LOGO
